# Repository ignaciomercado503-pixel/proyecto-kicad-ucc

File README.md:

# proyecto-kicad-ucc
Proyecto de microarduino trabajado en clases de Laboratorio de Computación.

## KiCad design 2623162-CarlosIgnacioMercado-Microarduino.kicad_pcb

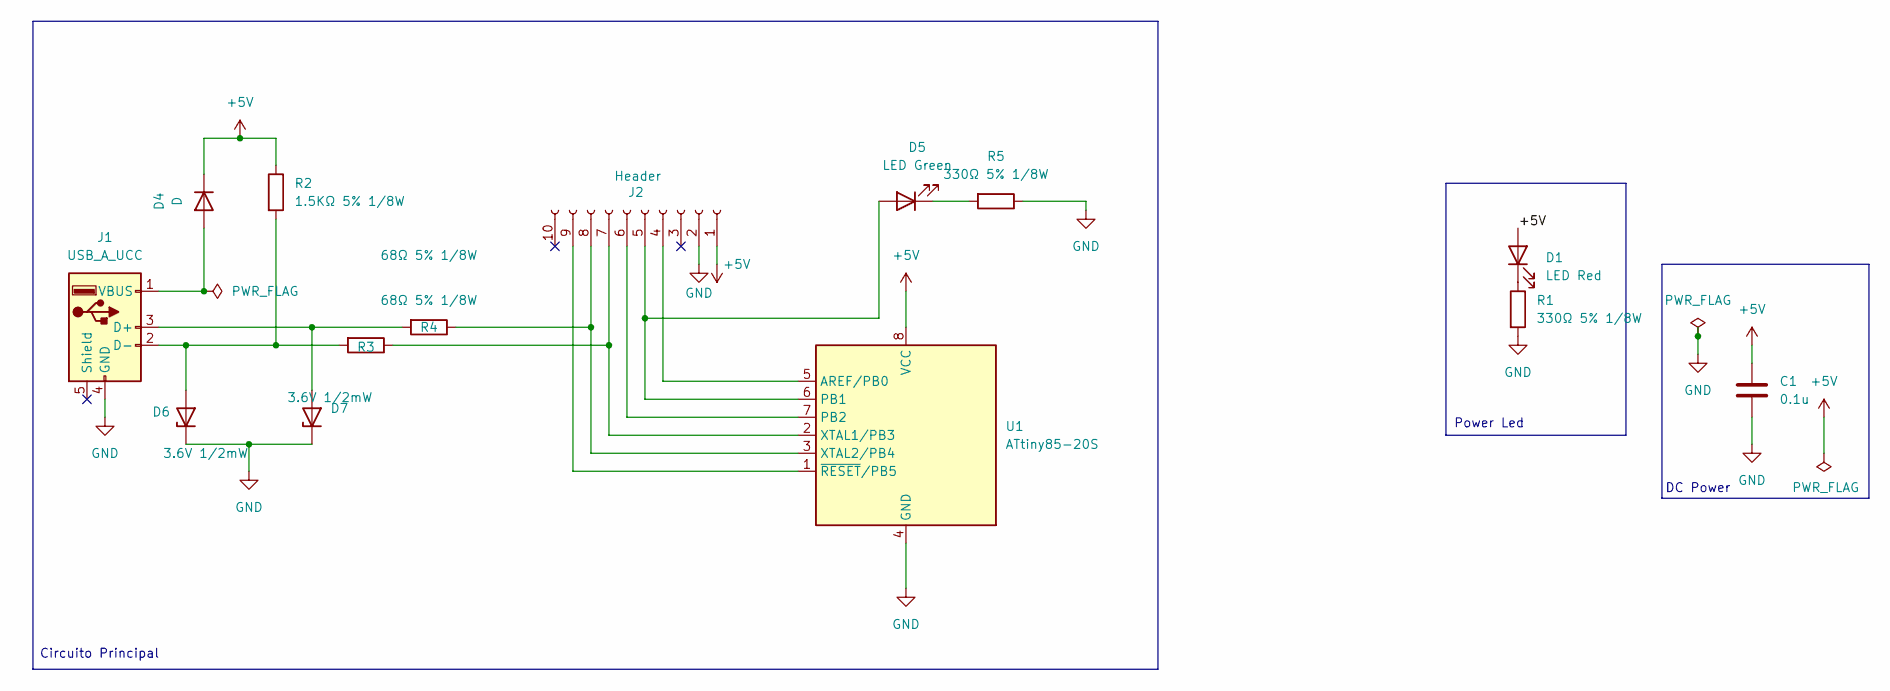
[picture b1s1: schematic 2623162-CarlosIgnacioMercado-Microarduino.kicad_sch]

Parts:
C1: 0.1u; C_0805_2012Metric_Pad1.18x1.45mm_HandSolder
D1: LED Red; LED.R
D4: D; D_MiniMELF
D5: LED Green; LED.R
D6, D7: 3.6V 1/2mW; D_SOD-123
J1: USB_A_UCC
J2: Header; PinSocket_1x10_P2.54mm_Vertical
R1, R5: 330Ω 5% 1/8W; R_0805_2012Metric_Pad1.20x1.40mm_HandSolder
R2: 1.5KΩ 5% 1/8W; R_0805_2012Metric_Pad1.20x1.40mm_HandSolder
R3, R4: 68Ω 5% 1/8W; R_0805_2012Metric_Pad1.20x1.40mm_HandSolder
U1: ATtiny85-20S; SOIC-8_5.3x5.3mm_P1.27mm

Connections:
+5V: C1.1, D1.2 (A), D4.1 (K), J2.1, R2.1, U1.8 (VCC)
GND: C1.2, D6.1 (K), D7.1 (K), J1.4 (GND), J2.2, R1.2, R5.1, U1.4 (GND)
unnamed: D1.1 (K), R1.1
unnamed: D4.2 (A), J1.1 (VBUS)
unnamed: D5.2 (A), J2.5, U1.6 (PB1)
unnamed: D5.1 (K), R5.2
unnamed: D6.2 (A), J1.2 (D-), R2.2, R3.2
unnamed: D7.2 (A), J1.3 (D+), R4.2
unnamed: J2.4, U1.5 (AREF/PB0)
unnamed: J2.6, U1.7 (PB2)
unnamed: J2.7, R3.1, U1.2 (XTAL1/PB3)
unnamed: J2.8, R4.1, U1.3 (XTAL2/PB4)
unnamed: J2.9, U1.1 (~RESET/PB5)

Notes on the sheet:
Circuito Principal
Power Led
DC Power

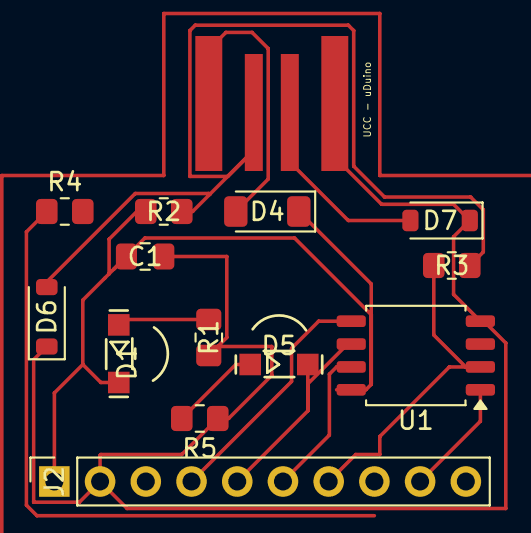
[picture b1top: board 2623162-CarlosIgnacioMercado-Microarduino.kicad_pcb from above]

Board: 2 copper layers, 14 parts (0 on the bottom side), 13 nets.

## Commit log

2026-04-14 Agrego proyecto kicad
2026-04-22 cambios en el proyecto
